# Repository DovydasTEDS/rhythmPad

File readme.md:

# RhythmPad

Have you played rhythm games and seen people use those cool keyboards with either just 4 keys, or 3 keys for games like osu!, osu!mania and Geometry Dash?  
The Rhythm Pad aims to be complatible with many rhythm games, such as the ones listed above.  
This should be compatible with VIA and should also be able to be used as a macropad.  

## Bill of Materials

Main Components:

- 5x Cherry MX switches
- 5x Blank DSA keycaps
- 1x EC11 Encoder
- 1x PCB
- 6x Through-hole 1N4148 Diodes
- 1x WS2812B LED / SK6812 MINI Led

Case Components:

- 5x M3 Heatset
- 5x M3x16 Bolt
- Top Case.step
- Bottom Case.step

Schematic            |  PCB         |   PCB (3d)
:-------------------------:|:-------------------------:|:-------------------------:|
    |    | 

Case (Assembled)            |  Case         
:-------------------------:|:-------------------------:|
    |

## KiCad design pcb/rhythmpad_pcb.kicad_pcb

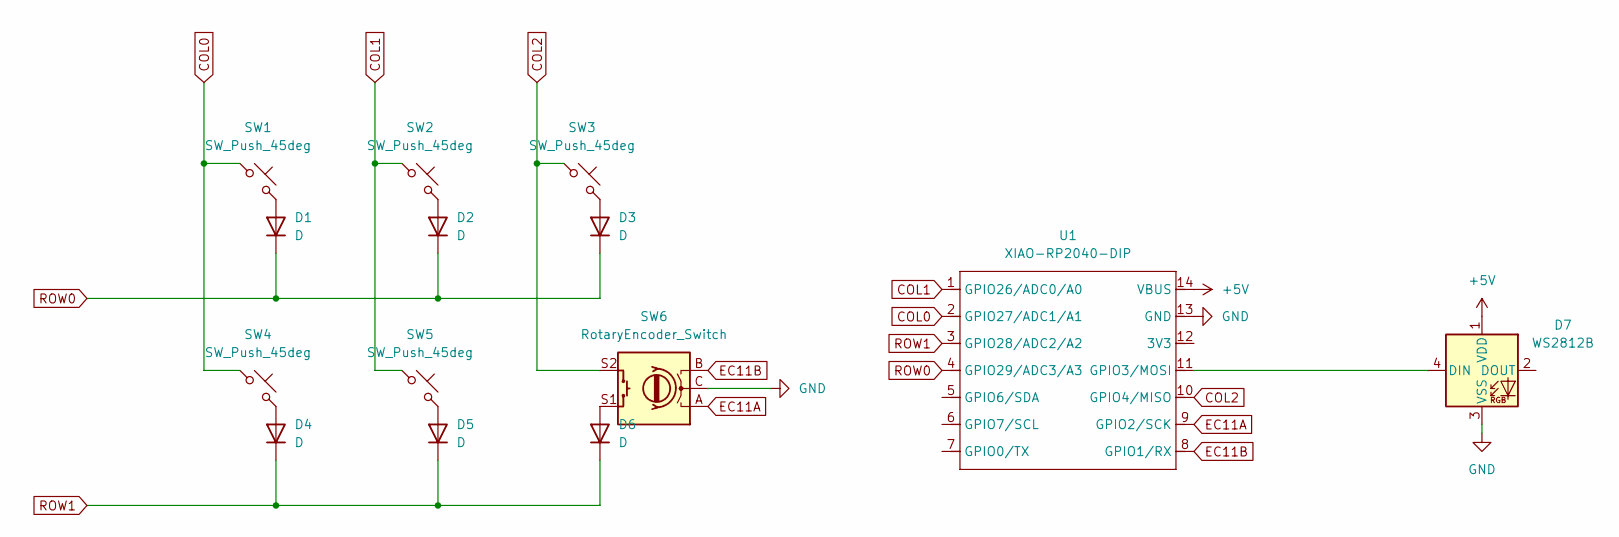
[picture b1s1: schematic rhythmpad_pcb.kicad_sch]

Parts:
D1, D2, D3, D4, D5, D6: D; D_DO-35_SOD27_P7.62mm_Horizontal
D7: WS2812B; LED_WS2812B_PLCC4_5.0x5.0mm_P3.2mm
SW1, SW2, SW3, SW4, SW5: SW_Push_45deg; MX-Solderable-1U
SW6: RotaryEncoder_Switch; RotaryEncoder_Alps_EC11E-Switch_Vertical_H20mm
U1: XIAO-RP2040-DIP

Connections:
+5V: D7.1 (VDD), U1.14 (VBUS)
COL0: SW1.1, SW4.1, U1.2 (GPIO27/ADC1/A1)
COL1: SW2.1, SW5.1, U1.1 (GPIO26/ADC0/A0)
COL2: SW3.1, SW6.S2, U1.10 (GPIO4/MISO)
EC11A: SW6.A, U1.9 (GPIO2/SCK)
EC11B: SW6.B, U1.8 (GPIO1/RX)
GND: D7.3 (VSS), SW6.C, U1.13 (GND)
unnamed: D1.2 (A), SW1.2
unnamed: D2.2 (A), SW2.2
unnamed: D3.2 (A), SW3.2
unnamed: D4.2 (A), SW4.2
unnamed: D5.2 (A), SW5.2
unnamed: D6.2 (A), SW6.S1
unnamed: D7.4 (DIN), U1.11 (GPIO3/MOSI)
ROW0: D1.1 (K), D2.1 (K), D3.1 (K), U1.4 (GPIO29/ADC3/A3)
ROW1: D4.1 (K), D5.1 (K), D6.1 (K), U1.3 (GPIO28/ADC2/A2)

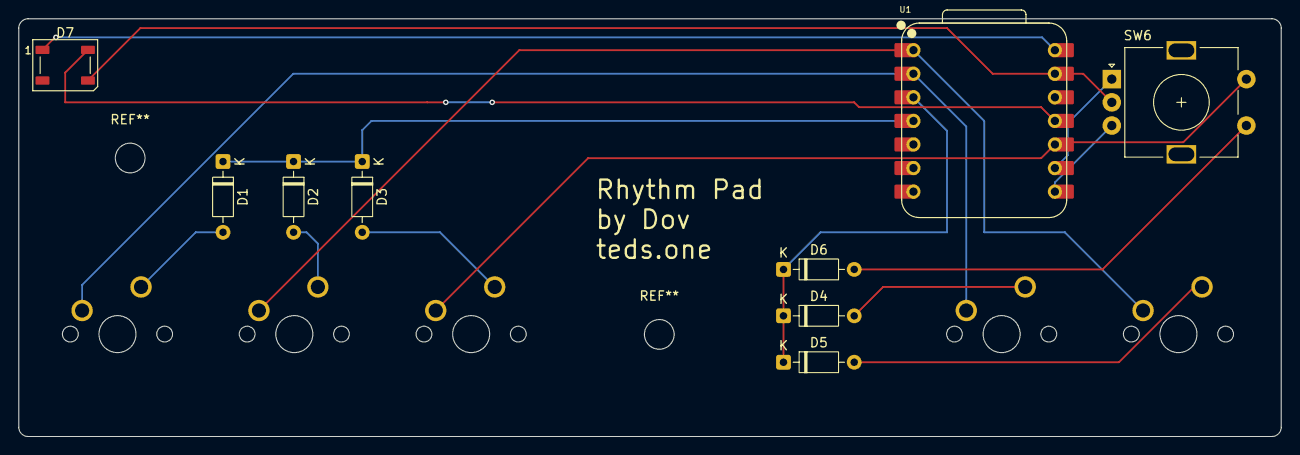
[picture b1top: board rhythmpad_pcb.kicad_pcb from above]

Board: 2 copper layers, 136.0 x 45.0 mm, 14 parts (0 on the bottom side), 16 nets.

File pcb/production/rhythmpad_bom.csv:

Designator,Footprint,Quantity,Value,LCSC Part #
"D1, D2, D3, D4, D5, D6",D_DO-35_SOD27_P7.62mm_Horizontal,6,D,
D7,LED_WS2812B_PLCC4_5.0x5.0mm_P3.2mm,1,WS2812B,
"SW1, SW2, SW3, SW4, SW5",MX-Solderable-1U,5,SW_Push_45deg,
SW6,RotaryEncoder_Alps_EC11E-Switch_Vertical_H20mm,1,RotaryEncoder_Switch,
U1,XIAO-RP2040-DIP,1,XIAO-RP2040-DIP,

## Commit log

2025-12-21 create
2025-12-21 add firmware
2025-12-21 Add Production files
2025-12-22 remake case
2025-12-22 Add gitignore
2025-12-23 fix gerbers
